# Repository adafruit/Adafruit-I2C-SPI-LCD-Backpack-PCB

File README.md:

# i2c / SPI character LCD backpack

<a href="http://www.adafruit.com/products/292"><br/>
Click here to purchase one from the Adafruit shop
</a>

LCD backpacks reduce the number of pins needed to connect to an LCD. LCDs are a fun and easy way to have your microcontroller project talk back to you. Character LCDs are common, and easy to get, available in tons of colors and sizes. [We've written tutorials on using character LCDs with an Arduino](http://learn.adafruit.com/character-lcds) (or similar microcontroller) but find that the number of pins necessary to control the LCD can be restrictive, especially with ambitious projects. We wanted to make a 'backpack' (add-on circuit) that would reduce the number of pins without a lot of expense.

By using simple i2c and SPI input/output expanders we have reduced the number of pins (only 2 pins are needed for i2c) while still making it easy to interface with the LCD. For Arduino users, we provide a easy-to-use library that is backwards compatible with projects using the '6 pin' wiring. The breakout comes with a 2-pin and 3-pin terminal block as shown (you can snap it together to make a 5-pin terminal and then solder it to the backpack for easy wiring)

This backpack will work with any 'standard' character LCD, from 8x1 to 20x4 sizes! As long as they have a 16-pin single-line connection header at the top. [We carry a few LCDs that work great](http://www.adafruit.com/category/63_96). We suggest using our blue & white 20x4 or 16x2 LCDs. It does not work with the 16x2 OLED displays. You can try to connect our RGB 16x2 or 20x4 LCDs up but this backpack will not control the RGB backlight so you'll have to use the backpack only for the 14 digital IO pins (pins #1-14) and connect the backlight pins (#15-#18) directly to your microcontroller with 4 extra wires for color/PWM control as if they were just an RGB LED.

<b>NEW! As of February 8, 2023 - This backpack now comes with a big re-spin that makes lots of improvements:</b>

* We've added a 3-5V boost circuit so you can use this backpack to control 5V LCDs even with 3V power and logic.
* The contrast potentiometer is a lot nicer and easier to twist using a small screwdriver
* Added SparkFun qwiic compatible STEMMA QT connectors for the I2C bus so you don't even need to solder the I2C and power lines. Just wire up to your favorite micro using a STEMMA QT adapter cable. QT Cable is not included, but we have a variety in the shop.
* Functionality and size/shape are the same - mechanically and code-wise it is a drop-in replacement.
* We've also updated this PCB with Adafruit Pinguin to make a lovely and legible silkscreen.

For advanced users, this project can be used for general purpose I/O expansion, the MCP23008 has 8 i/o pins (7 are connected) with optional pull-ups, the SPI 74HC595 has 7 connected outputs.

Note: The terminal blocks included with your product may be blue or black.

[For a detailed tutorial on usage, including an Arduino library, wiring diagrams, and files, please visit the product page](http://learn.adafruit.com/i2c-spi-lcd-backpack)

### License

Adafruit invests time and resources providing this open source design, please support Adafruit and open-source hardware by purchasing products from [Adafruit](https://www.adafruit.com)!

Designed by Limor Fried/Ladyada for Adafruit Industries.

Creative Commons Attribution/Share-Alike, all text above must be included in any redistribution. See license.txt for additional details.

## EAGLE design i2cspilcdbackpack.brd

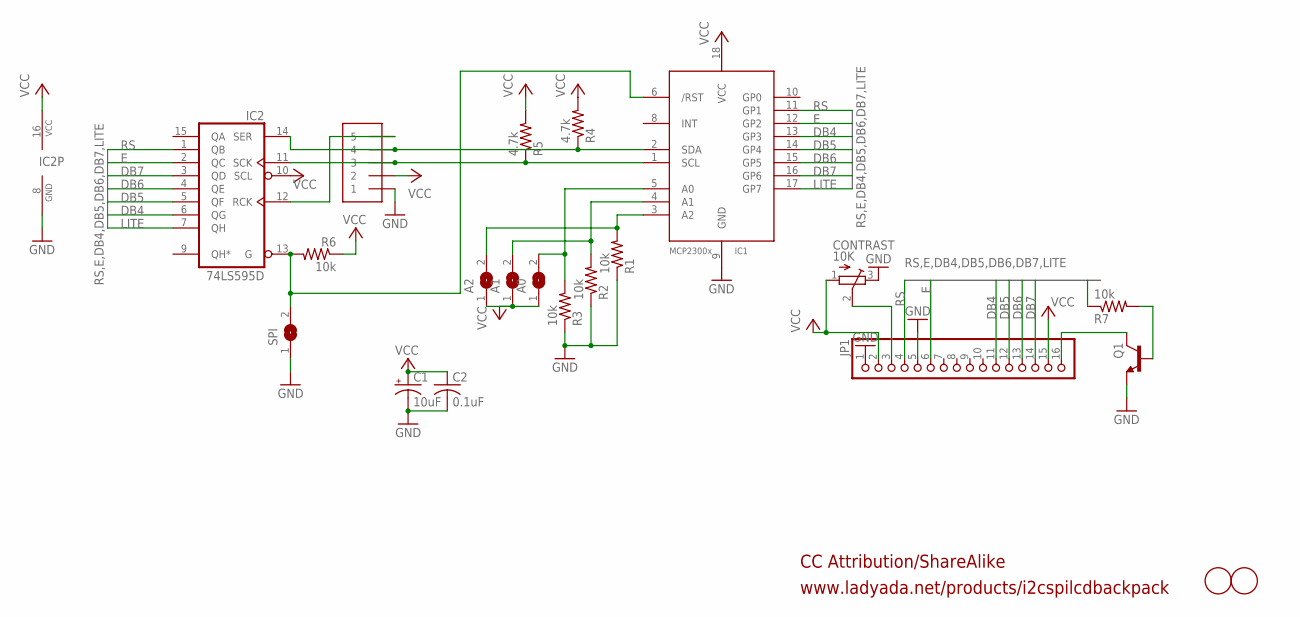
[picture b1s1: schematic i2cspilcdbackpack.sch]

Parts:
A0, A1, A2: SJ
C1: 10uF; A/3216-18R
C2: 0.1uF; C0805K
CONTRAST: 10K; TC33X
IC1: MCP2300X/SO; SO18W
IC2: 74LS595D; SO16
J1: 1X5; 3.5MM-5P
JP1: PINHD-1X16; 1X16
Q1: MMBT2222ALT1-NPN-SOT23-BEC; SOT23-BEC
R1, R2, R3, R6, R7: 10k; R0805
R4, R5: 4.7k; R0805
SPI: SJ
U$1, U$2: FIDUCIAL; FIDUCIAL_1MM

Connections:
CLOCK: IC1.1 (SCL), IC2.11 (SCK), J1.3, R5.1
DATA: IC1.2 (SDA), IC2.14 (SER), J1.4, R4.1
DB4: IC1.13 (GP3), IC2.6 (QG), JP1.11
DB5: IC1.14 (GP4), IC2.5 (QF), JP1.12
DB6: IC1.15 (GP5), IC2.4 (QE), JP1.13
DB7: IC1.16 (GP6), IC2.3 (QD), JP1.14
E: IC1.12 (GP2), IC2.2 (QC), JP1.6
GND: C1.-, C2.2, CONTRAST.3 (E), IC1.9 (GND), IC2.8 (GND), J1.1, JP1.1, JP1.5, Q1.E, R1.1, R2.1, R3.1, SPI.1
LATCH: IC2.12 (RCK), J1.5
LITE: IC1.17 (GP7), IC2.7 (QH), R7.1
unnamed: A0.2, IC1.5 (A0), R3.2
unnamed: A1.2, IC1.4 (A1), R2.2
unnamed: A2.2, IC1.3 (A2), R1.2
unnamed: IC1.6 (/RST), IC2.13 (G), R6.2, SPI.2
unnamed: JP1.16, Q1.C
unnamed: Q1.B, R7.2
unnamed: CONTRAST.2 (S), JP1.3
RS: IC1.11 (GP1), IC2.1 (QB), JP1.4
VCC: A0.1, A1.1, A2.1, C1.+, C2.1, CONTRAST.1 (A), IC1.18 (VCC), IC2.10 (SCL), IC2.16 (VCC), J1.2, JP1.2, JP1.15, R4.2, R5.2, R6.1

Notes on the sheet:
www.ladyada.net/products/i2cspilcdbackpack
CC Attribution/ShareAlike

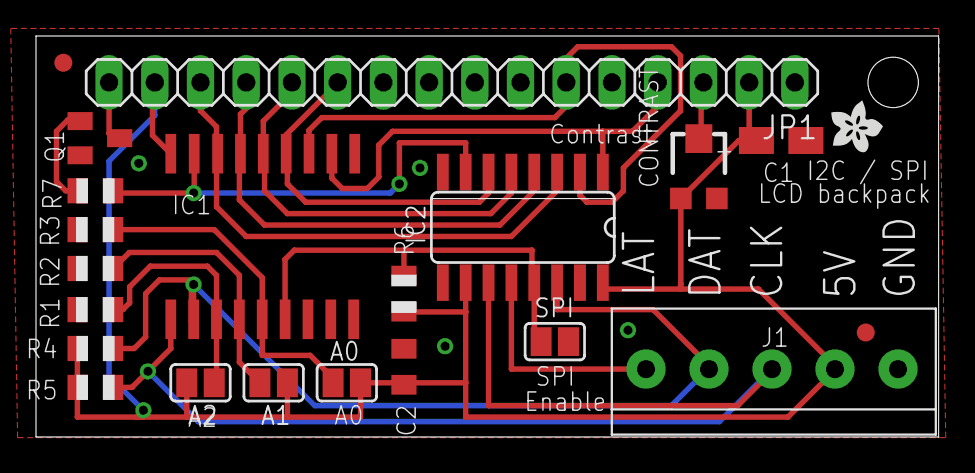
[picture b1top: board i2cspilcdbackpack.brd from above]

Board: 2 copper layers, 50.1 x 22.3 mm, 22 parts (0 on the bottom side), 19 nets.

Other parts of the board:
U$3: ADAFRUIT200MIL

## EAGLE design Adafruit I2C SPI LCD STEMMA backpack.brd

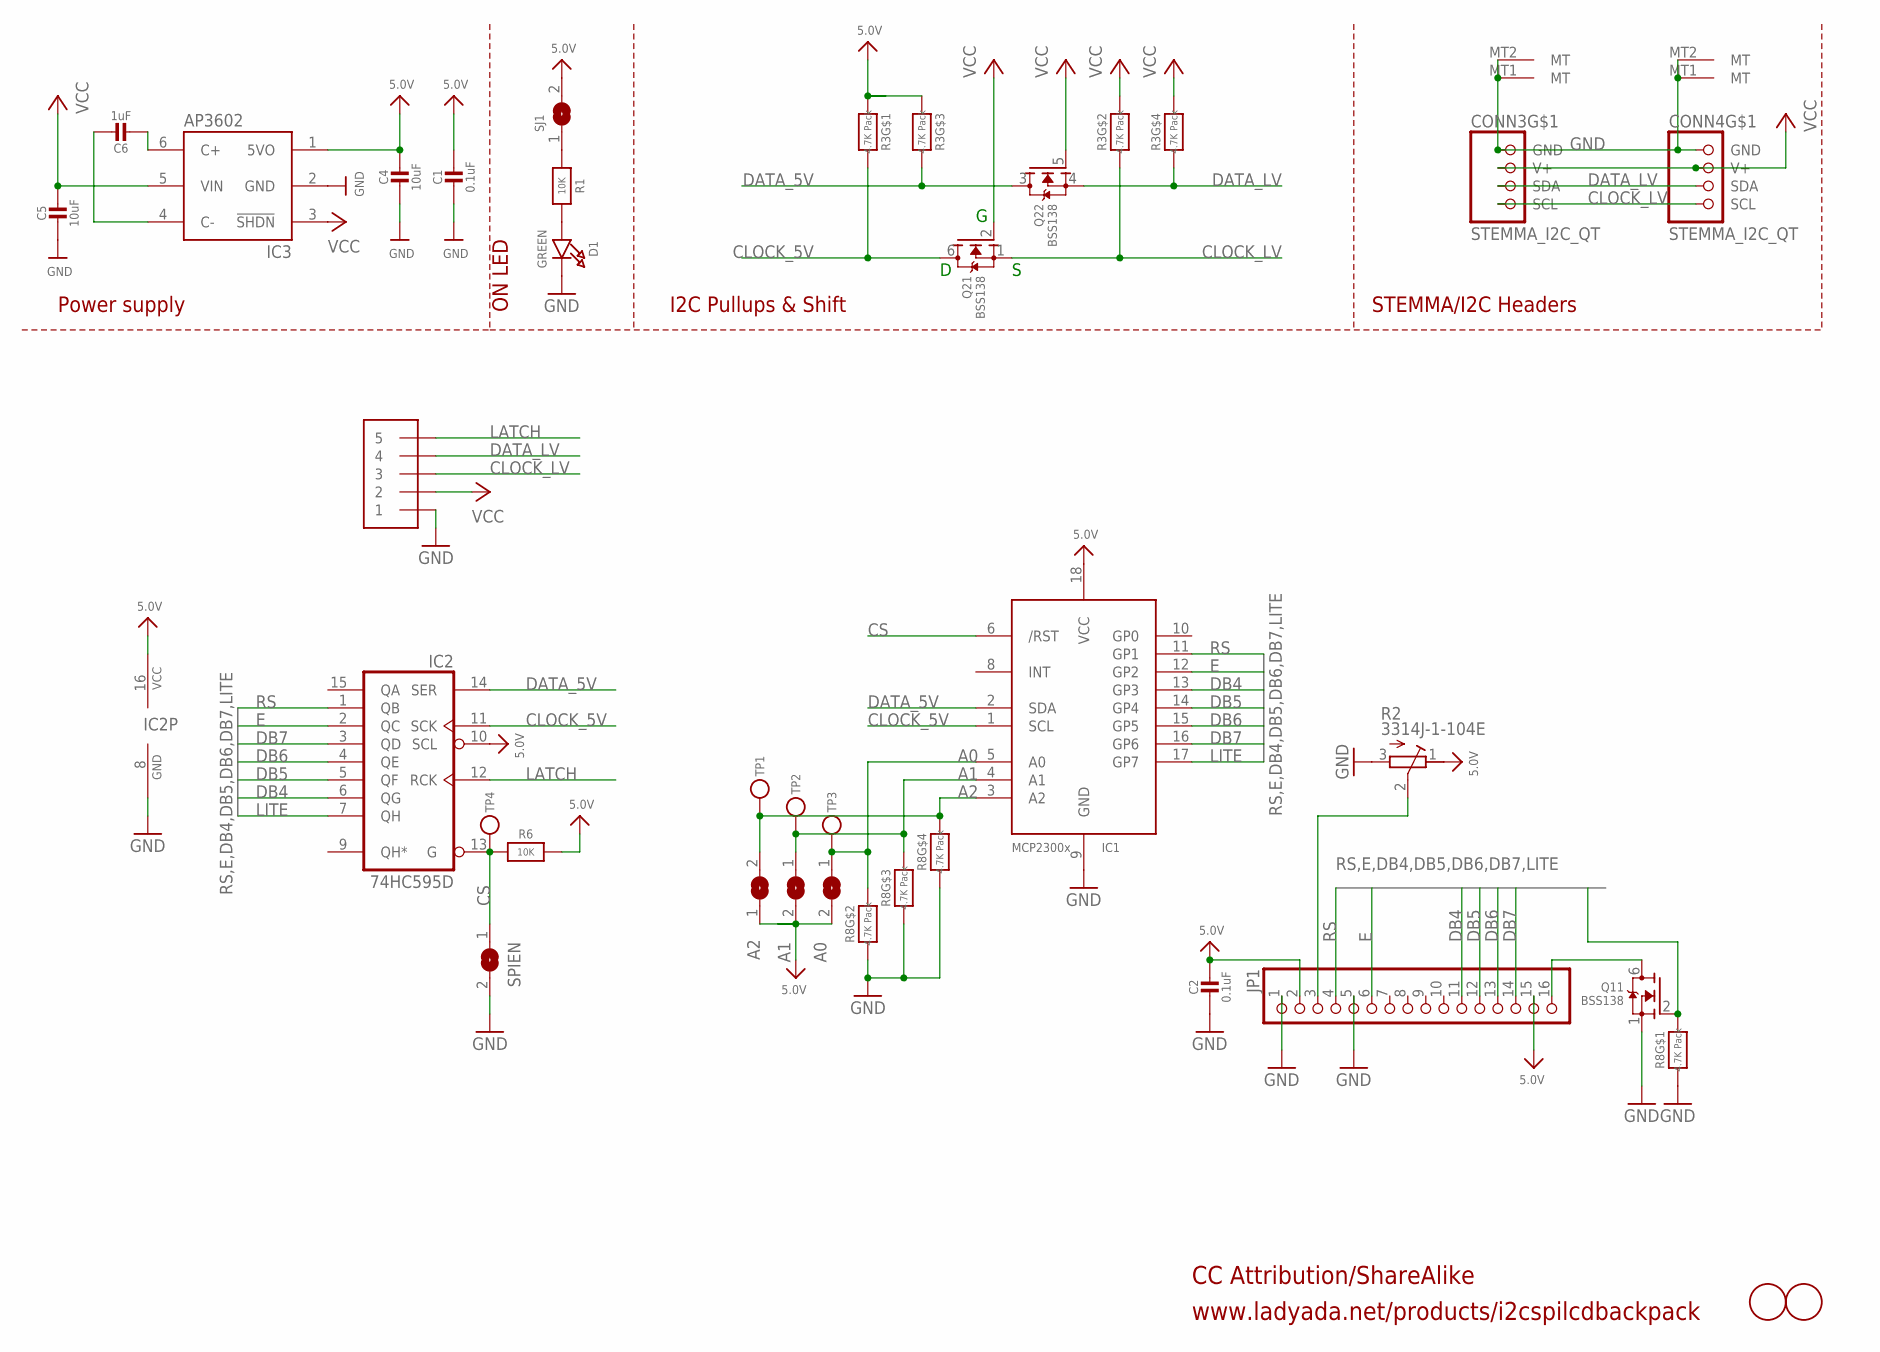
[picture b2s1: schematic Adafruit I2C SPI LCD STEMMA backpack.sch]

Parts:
A0, A1, A2: SOLDERJUMPER; SOLDERJUMPER_ARROW_NOPASTE
C1, C2: 0.1uF; 0603-NO
C4, C5: 10uF; 0805-NO
C6: 1uF; 0805-NO
CONN3, CONN4: STEMMA_I2C_QT; JST_SH4
D1: GREEN; CHIPLED_0603_NOOUTLINE
IC1: MCP23008/SO; SO18W
IC2: 74HC595D; SO16
IC3: AP3602/RT9361; SOT23-6
J1: 1X5; 1X05-3.5MM
JP1: PINHD-1X16; 1X16
Q1, Q2: BSS138; SOT363
R1, R6: 10K; 0603-NO
R2: 3314J-1-104E; RTRIM3314J
R3, R8: 4.7K Pack; RESPACK_4X0603
SJ1: SOLDERJUMPERCLOSED; SOLDERJUMPER_CLOSEDWIRE
SPIEN: SOLDERJUMPER; SOLDERJUMPER_ARROW_NOPASTE
TP1, TP2, TP3, TP4: TESTPOINTROUND1.5MM; TESTPOINT_ROUND_1.5MM
U$1, U$2: FIDUCIAL; FIDUCIAL_1MM

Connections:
5.0V: A0.2, A1.2, A2.1, C1.1, C2.1, C4.1, IC1.18 (VCC), IC2.10 (SCL), IC2.16 (VCC), IC3.1 (5VO), JP1.2, JP1.15, R2.1 (E), R3.1, R3.3 (1), R6.1, SJ1.2
A0: A0.1, IC1.5 (A0), R8.7 (2), TP3.P$1
A1: A1.1, IC1.4 (A1), R8.6 (2), TP2.P$1
A2: A2.2, IC1.3 (A2), R8.5 (2), TP1.P$1
CLOCK_5V: IC1.1 (SCL), IC2.11 (SCK), Q2.6 (D), R3.8 (2)
CLOCK_LV: CONN3.4 (SCL), CONN4.4 (SCL), J1.3, Q2.1 (S), R3.7 (2)
CONTRAST: JP1.3, R2.2 (S)
CS: IC1.6 (/RST), IC2.13 (G), R6.2, SPIEN.1, TP4.P$1
DATA_5V: IC1.2 (SDA), IC2.14 (SER), Q2.3 (D), R3.6 (2)
DATA_LV: CONN3.3 (SDA), CONN4.3 (SDA), J1.4, Q2.4 (S), R3.5 (2)
DB4: IC1.13 (GP3), IC2.6 (QG), JP1.11
DB5: IC1.14 (GP4), IC2.5 (QF), JP1.12
DB6: IC1.15 (GP5), IC2.4 (QE), JP1.13
DB7: IC1.16 (GP6), IC2.3 (QD), JP1.14
E: IC1.12 (GP2), IC2.2 (QC), JP1.6
GND: C1.2, C2.2, C4.2, C5.2, CONN3.1 (GND), CONN3.MT1 (MT), CONN3.MT2 (MT), CONN4.1 (GND), CONN4.MT1 (MT), CONN4.MT2 (MT), D1.C, IC1.9 (GND), IC2.8 (GND), IC3.2 (GND), J1.1, JP1.1, JP1.5, Q1.1 (S), R2.3 (A), R8.1, R8.2 (1), R8.3 (1), R8.4 (1), SPIEN.2
LATCH: IC2.12 (RCK), J1.5
LEDK: JP1.16, Q1.6 (D)
LITE: IC1.17 (GP7), IC2.7 (QH), Q1.2 (G), R8.8 (2)
unnamed: D1.A, R1.2
unnamed: R1.1, SJ1.1
unnamed: C6.2, IC3.6 (C+)
unnamed: C6.1, IC3.4 (C-)
RS: IC1.11 (GP1), IC2.1 (QB), JP1.4
VCC: C5.1, CONN3.2 (V+), CONN4.2 (V+), IC3.3 (!SHDN), IC3.5 (VIN), J1.2, Q2.2 (G), Q2.5 (G), R3.2 (1), R3.4 (1)

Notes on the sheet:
www.ladyada.net/products/i2cspilcdbackpack
CC Attribution/ShareAlike
I2C Pullups & Shift
STEMMA/I2C Headers
ON LED
Power supply

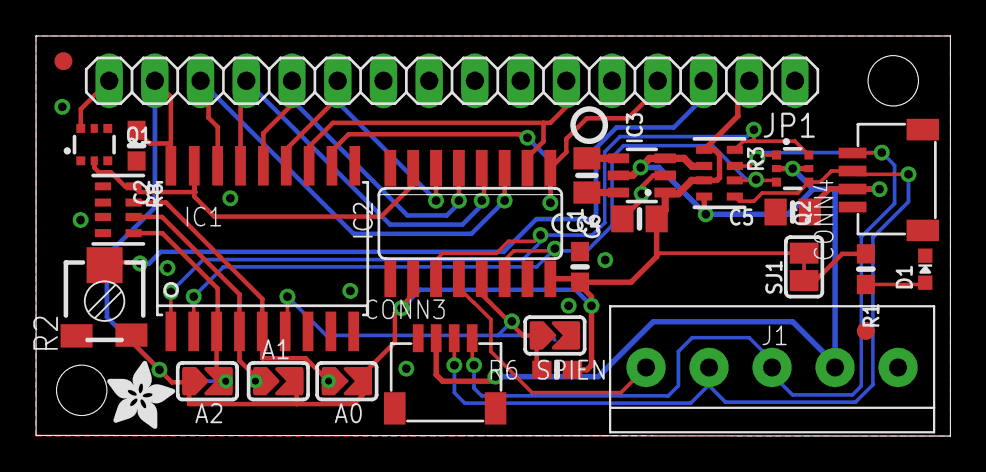
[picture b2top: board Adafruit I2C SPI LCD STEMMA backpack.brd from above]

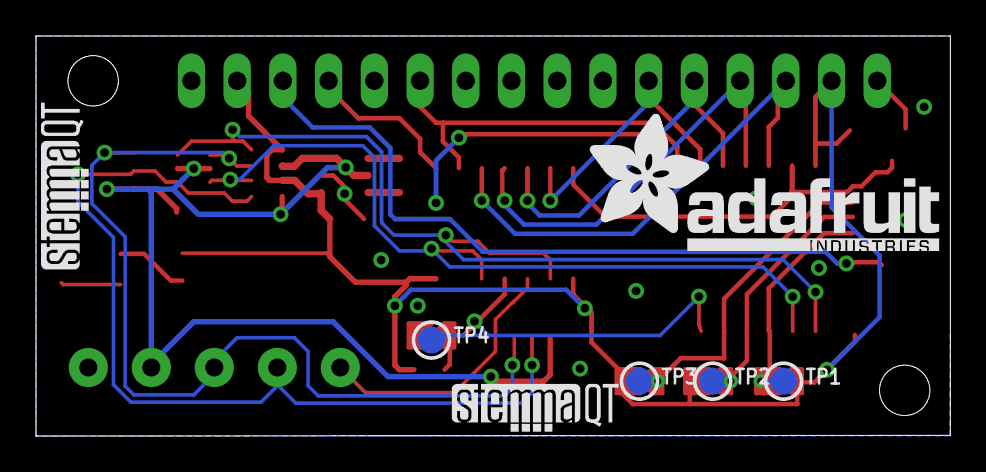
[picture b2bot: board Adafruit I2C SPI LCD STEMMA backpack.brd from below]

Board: 2 copper layers, 50.8 x 22.2 mm, 49 parts (8 on the bottom side), 25 nets.

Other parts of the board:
PLABEL0: PLABEL0
PLABEL1: PLABEL1
PLABEL2: PLABEL2
PLABEL3: PLABEL3
PLABEL4: PLABEL4
PLABEL5: PLABEL5
PLABEL6: PLABEL6
PLABEL7: PLABEL7
PLABEL8: PLABEL8
PLABEL9: PLABEL9
PLABEL10: PLABEL10
PLABEL11: PLABEL11
PLABEL12: PLABEL12
U$4: ADAFRUIT_3.5MM
U$7: PCBFEAT-REV-040
U$11, U$12: STEMMAQT
U$23: ADAFRUIT_TEXT_20MM

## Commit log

2010-11-02 added a PNG image
2011-12-19 clarified MCP23008 connections
2019-03-28 readme + image
2023-02-13 adding STEMMA version
2026-06-03 update file format to XML

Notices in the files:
parts and their libraries:
microbuilder: This work is placed in the public domain, and may be freely used for commercial and non-commercial work with the following conditions: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
